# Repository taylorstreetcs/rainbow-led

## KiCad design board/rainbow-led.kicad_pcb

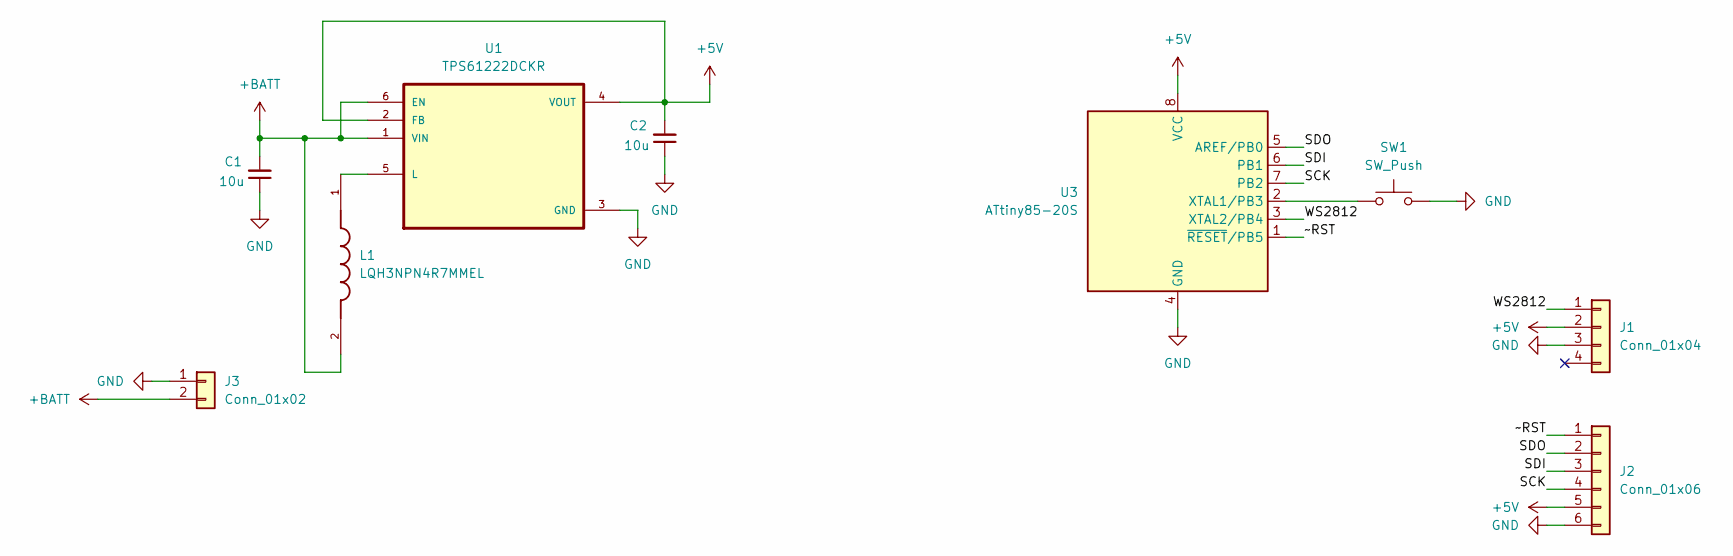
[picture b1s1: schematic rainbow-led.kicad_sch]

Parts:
C1, C2: 10u; C_0402_1005Metric_Pad0.74x0.62mm_HandSolder
J1: Conn_01x04; Pads_1x04_P1.27mm
J2: Conn_01x06; Pads_1x06_P1.27mm
J3: Conn_01x02; Pads_1x02_P2.54mm
L1: LQH3NPN4R7MMEL; IND_LQH3NPN4R7MMEL; PARTREV N/A
SW1: SW_Push; SW_SPST_TL3305B
U1: TPS61222DCKR; SOT65P210X110-6N
U3: ATtiny85-20S; SOIC-8_5.3x5.3mm_P1.27mm

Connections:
+5V: C2.2, J1.2, J2.5, U1.2 (FB), U1.4 (VOUT), U3.8 (VCC)
+BATT: C1.2, J3.2, L1.2, U1.1 (VIN), U1.6 (EN)
/SCK: J2.4, U3.7 (PB2)
/SDI: J2.3, U3.6 (PB1)
/SDO: J2.2, U3.5 (AREF/PB0)
/WS2812: J1.1, U3.3 (XTAL2/PB4)
/~RST: J2.1, U3.1 (~RESET/PB5)
GND: C1.1, C2.1, J1.3, J2.6, J3.1, SW1.2, U1.3 (GND), U3.4 (GND)
unnamed: L1.1, U1.5 (L)
unnamed: SW1.1, U3.2 (XTAL1/PB3)

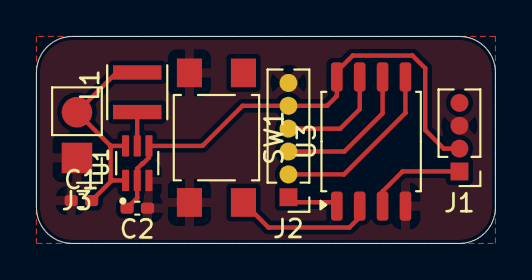
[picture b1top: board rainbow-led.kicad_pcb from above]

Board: 2 copper layers, 25.5 x 11.5 mm, 9 parts (0 on the bottom side), 10 nets.

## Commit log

2025-09-12 First design of board.
2025-09-13 Switch inductor to recommended one.
2025-09-13 Update fill.
